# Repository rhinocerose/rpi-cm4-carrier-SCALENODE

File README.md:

# Scalenode platform

Copyright (c) 2020-2021 [Antmicro](https://www.antmicro.com>)

[Home Page](https://opensource.antmicro.com/projects/scalenode)

## Overview

This repository contains the PCB design files for a baseboard supporting Raspberry Pi Compute Module 4.
The baseboard has been optimized for 19-inch rack mount installations for distributed multi-node computing systems.

## Key features

* Supports Raspberry Pi CM4
* Gigabit Ethernet with integrated PoE circuitry
* On-board M.2 (key-M) slot supporting NVMe SSDs 
* Slim PCB outline for 1U chassis
* Expansion connector for peripherals connected over USB
* Expansion connector for HDMI adapters

## Board layout and dimensions

## Design status

The PCB design files were prepared in KiCad.
Prototypes of revision 1.0.0 are now being verified.

## License

[Apache-2.0](LICENSE)

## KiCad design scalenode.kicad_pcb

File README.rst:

==================
Scalenode platform
==================

Copyright (c) 2020-2021 `Antmicro <https://www.antmicro.com>`_

`Home Page <https://opensource.antmicro.com/projects/scalenode>`_

.. figure:: img/scalenode.jpg

Overview
========

This repository contains the PCB design files for a baseboard supporting Raspberry Pi Compute Module 4.
The baseboard has been optimized for 19-inch rack mount installations for distributed multi-node computing systems.

Key features
============

* Supports Raspberry Pi CM4
* Gigabit Ethernet with integrated PoE circuitry
* On-board M.2 (key-M) slot supporting NVMe SSDs 
* Slim PCB outline for 1U chassis
* Expansion connector for peripherals connected over USB
* Expansion connector for HDMI adapters

Board layout and dimensions
===========================

.. image:: img/scalenode-dimensions.png
   :align: center

Design status
=============

The PCB design files were prepared in KiCad.
Prototypes of revision 1.0.0 are now being verified.

License
=======

`Apache-2.0 <LICENSE>`_

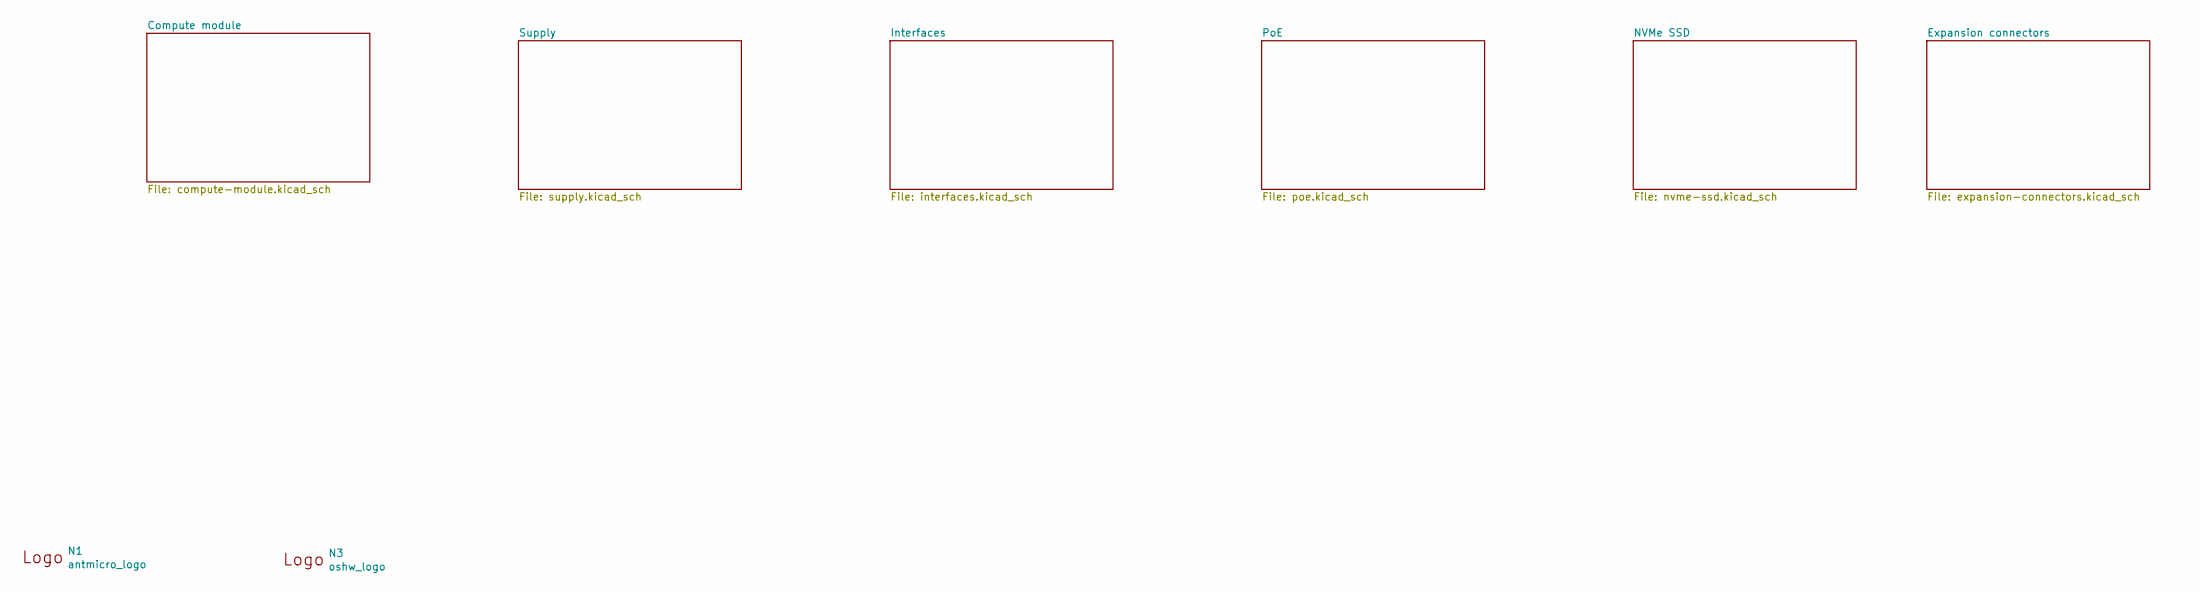
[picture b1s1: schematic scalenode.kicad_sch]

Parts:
N1: antmicro_logo; antmicro-logo_scaled_15mm
N3: oshw_logo; oshw-logo

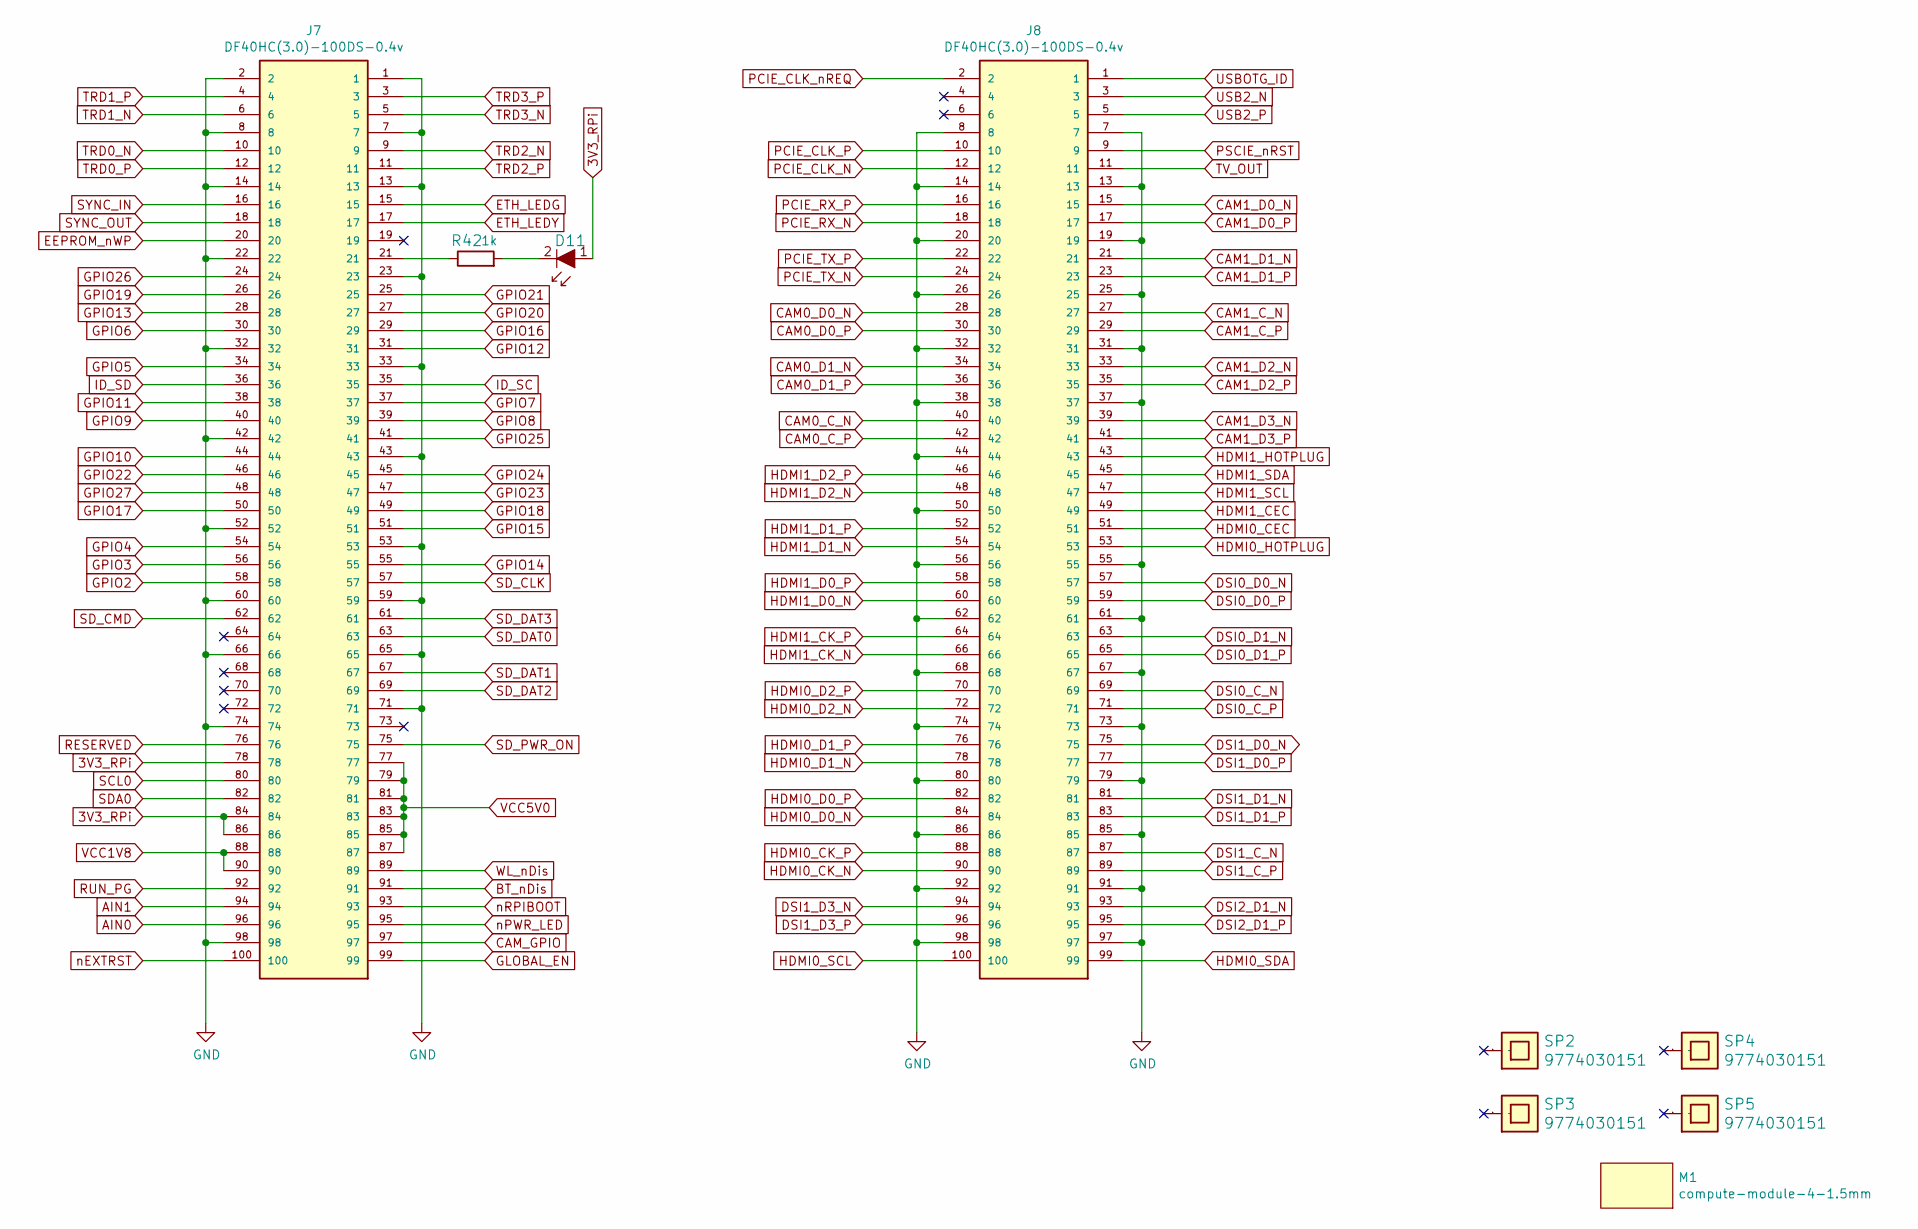
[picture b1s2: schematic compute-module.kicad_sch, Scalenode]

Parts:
D11: KP-1608CGCK; LED_0603; MPN KP-1608CGCK
J7, J8: DF40HC(3.0)-100DS-0.4v; DF40HC-3.0-100DS-0.4v
M1: compute-module-4-1.5mm
R42: R_1k_0603; 0603-res; MPN CR0603-JW-102ELF
SP2, SP3, SP4, SP5: 9774030151; MPN 9774030151

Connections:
AIN0: J7.96
AIN1: J7.94
BT_nDis: J7.91
CAM0_C_N: J8.40
CAM0_C_P: J8.42
CAM0_D0_N: J8.28
CAM0_D0_P: J8.30
CAM0_D1_N: J8.34
CAM0_D1_P: J8.36
CAM1_C_N: J8.27
CAM1_C_P: J8.29
CAM1_D0_N: J8.15
CAM1_D0_P: J8.17
CAM1_D1_N: J8.21
CAM1_D1_P: J8.23
CAM1_D2_N: J8.33
CAM1_D2_P: J8.35
CAM1_D3_N: J8.39
CAM1_D3_P: J8.41
CAM_GPIO: J7.97
DSI0_C_N: J8.69
DSI0_C_P: J8.71
DSI0_D0_N: J8.57
DSI0_D0_P: J8.59
DSI0_D1_N: J8.63
DSI0_D1_P: J8.65
DSI1_C_N: J8.87
DSI1_C_P: J8.89
DSI1_D0_N: J8.75
DSI1_D0_P: J8.77
DSI1_D1_N: J8.81
DSI1_D1_P: J8.83
DSI1_D3_N: J8.94
DSI1_D3_P: J8.96
DSI2_D1_N: J8.93
DSI2_D1_P: J8.95
EEPROM_nWP: J7.20
ETH_LEDG: J7.15; also elsewhere on the board
ETH_LEDY: J7.17; also elsewhere on the board
GLOBAL_EN: J7.99
GND: J7.1, J7.2, J7.7, J7.8, J7.13, J7.14, J7.22, J7.23, J7.32, J7.33, J7.42, J7.43, J7.52, J7.53, J7.59, J7.60, J7.65, J7.66, J7.71, J7.74, J7.98, J8.7, J8.8, J8.13, J8.14, J8.19, J8.20, J8.25, J8.26, J8.31, J8.32, J8.37, J8.38, J8.44, J8.50, J8.55, J8.56, J8.61, J8.62, J8.67, J8.68, J8.73, J8.74, J8.79, J8.80, J8.85, J8.86, J8.91, J8.92, J8.97, J8.98; also elsewhere on the board
GPIO2: J7.58
GPIO3: J7.56; also elsewhere on the board
GPIO4: J7.54
GPIO5: J7.34
GPIO6: J7.30
GPIO7: J7.37
GPIO8: J7.39
GPIO9: J7.40
GPIO10: J7.44
GPIO11: J7.38
GPIO12: J7.31
GPIO13: J7.28
GPIO14: J7.55
GPIO15: J7.51
GPIO16: J7.29
GPIO17: J7.50
GPIO18: J7.49
GPIO19: J7.26
GPIO20: J7.27
GPIO21: J7.25
GPIO22: J7.46
GPIO23: J7.47
GPIO24: J7.45
GPIO25: J7.41
GPIO26: J7.24
GPIO27: J7.48
HDMI0_CEC: J8.51
HDMI0_CK_N: J8.90
HDMI0_CK_P: J8.88
HDMI0_D0_N: J8.84
HDMI0_D0_P: J8.82
HDMI0_D1_N: J8.78
HDMI0_D1_P: J8.76
HDMI0_D2_N: J8.72
HDMI0_D2_P: J8.70
HDMI0_HOTPLUG: J8.53
HDMI0_SCL: J8.100
HDMI0_SDA: J8.99
HDMI1_CEC: J8.49
HDMI1_CK_N: J8.66
HDMI1_CK_P: J8.64
HDMI1_D0_N: J8.60
HDMI1_D0_P: J8.58
HDMI1_D1_N: J8.54
HDMI1_D1_P: J8.52
HDMI1_D2_N: J8.48
HDMI1_D2_P: J8.46
HDMI1_HOTPLUG: J8.43
HDMI1_SCL: J8.47
HDMI1_SDA: J8.45
ID_SC: J7.35
ID_SD: J7.36
unnamed: D11.2, R42.2
unnamed: J7.21, R42.1
PCIE_CLK_N: J8.12; also elsewhere on the board
PCIE_CLK_P: J8.10; also elsewhere on the board
PCIE_CLK_nREQ: J8.2; also elsewhere on the board
PCIE_RX_N: J8.18; also elsewhere on the board
PCIE_RX_P: J8.16; also elsewhere on the board
PCIE_TX_N: J8.24; also elsewhere on the board
PCIE_TX_P: J8.22; also elsewhere on the board
PSCIE_nRST: J8.9; also elsewhere on the board
RESERVED: J7.76
RUN_PG: J7.92
SCL0: J7.80
SDA0: J7.82
SD_CLK: J7.57; also elsewhere on the board
SD_CMD: J7.62; also elsewhere on the board
SD_DAT0: J7.63; also elsewhere on the board
SD_DAT1: J7.67; also elsewhere on the board
SD_DAT2: J7.69; also elsewhere on the board
SD_DAT3: J7.61; also elsewhere on the board
SD_PWR_ON: J7.75
SYNC_IN: J7.16
SYNC_OUT: J7.18
TRD0_N: J7.10; also elsewhere on the board
TRD0_P: J7.12; also elsewhere on the board
TRD1_N: J7.6; also elsewhere on the board
TRD1_P: J7.4; also elsewhere on the board
TRD2_N: J7.9; also elsewhere on the board
TRD2_P: J7.11; also elsewhere on the board
TRD3_N: J7.5; also elsewhere on the board
TRD3_P: J7.3; also elsewhere on the board
TV_OUT: J8.11
USB2_N: J8.3; also elsewhere on the board
USB2_P: J8.5; also elsewhere on the board
USBOTG_ID: J8.1; also elsewhere on the board
VCC1V8: J7.88, J7.90
VCC5V0: J7.77, J7.79, J7.81, J7.83, J7.85, J7.87; also elsewhere on the board
WL_nDis: J7.89
nEXTRST: J7.100
nPWR_LED: J7.95
nRPIBOOT: J7.93

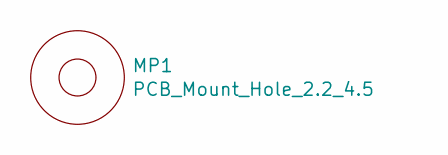
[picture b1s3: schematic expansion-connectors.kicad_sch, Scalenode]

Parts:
MP1: PCB_Mount_Hole_2.2_4.5; mounting-hole-2.2mm

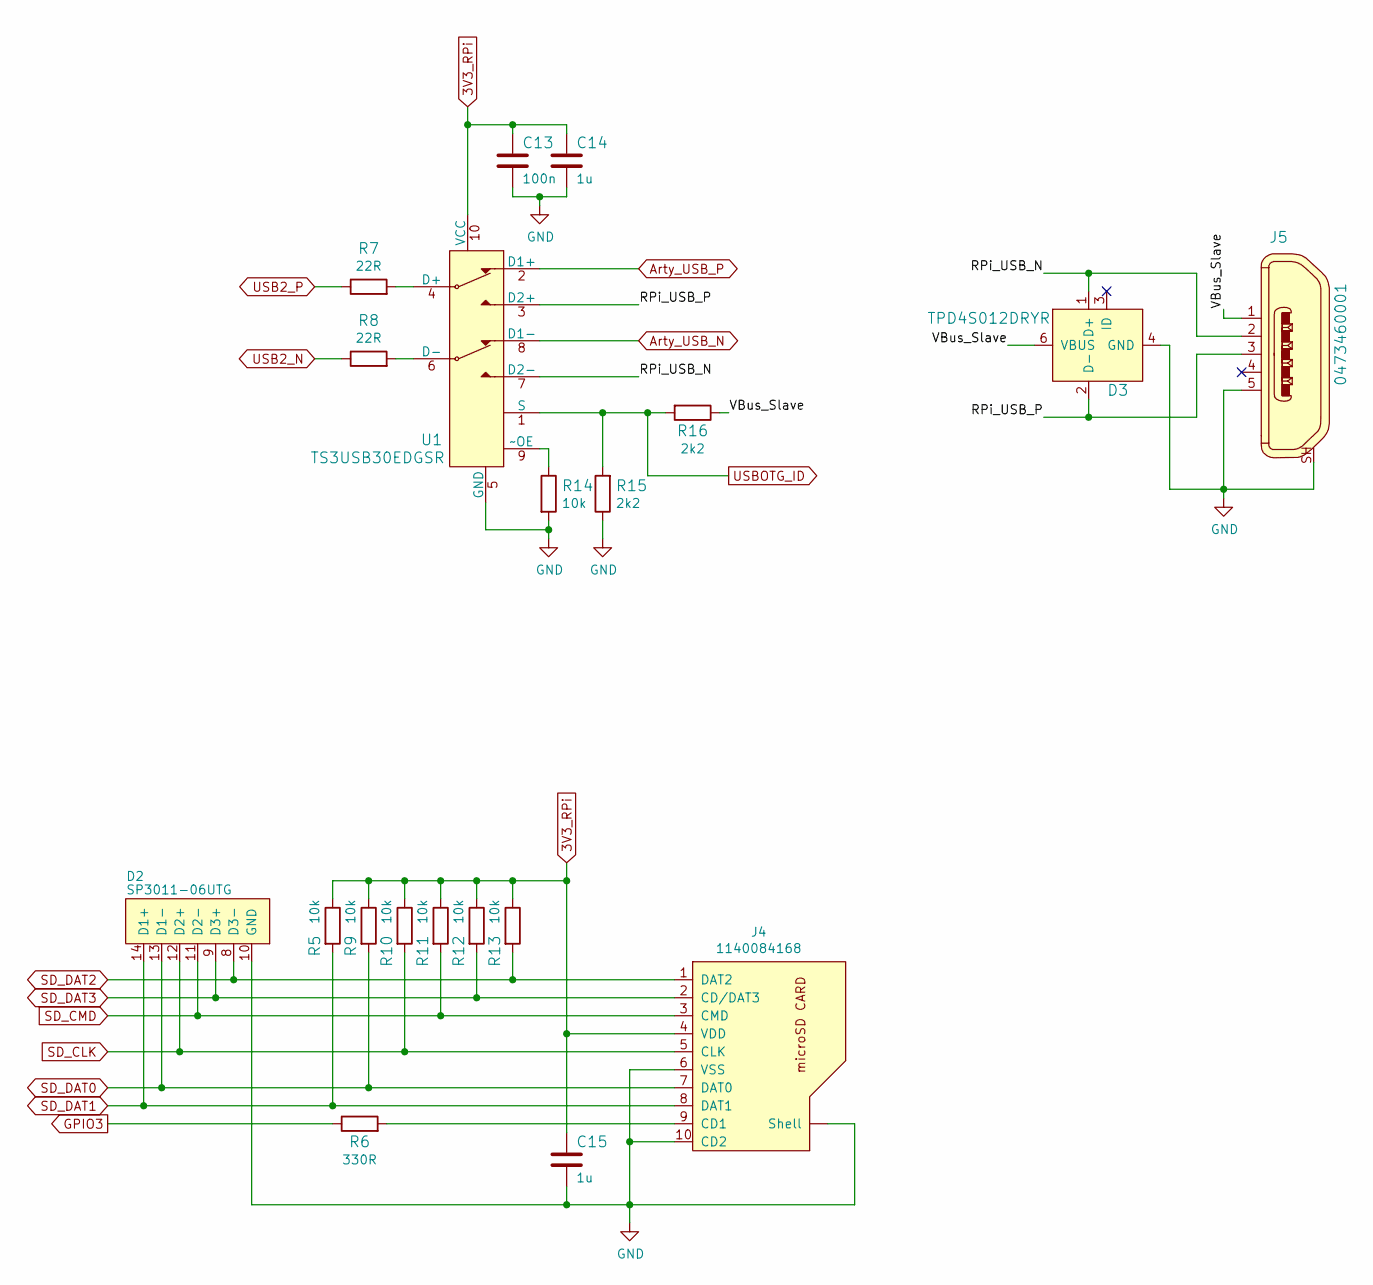
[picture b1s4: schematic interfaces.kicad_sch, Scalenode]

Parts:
C13: C_100n_0402; 0402-cap; MPN 0402X104K6R3CT
C14, C15: C_1u_0402; 0402-cap; MPN C1005X6S1A105K050BC
D2: SP3011-06UTG; SON50P350X135X55-14N; MPN SP3011-06UTG
D3: TPD4S012DRYR; UFDFN-6_1.45x1mm; MPN TPD4S012DRYR
J4: 1140084168; MicroSD_1140084168; MPN 1140084168
J5: 0473460001; USB_Micro_B_Female_0473460001; MPN 0473460001
R5, R9, R10, R11, R12, R13, R14: R_10k_0402; 0402-res; MPN CRCW040210K0FKEDHP
R6: R_330R_0402; 0402-res; MPN MCMR04X3300FTL
R7, R8: R_22R_0402; 0402-res; MPN CRCW040222R0FKED
R15, R16: R_2k2_0402; 0402-res; MPN RC0402FR-072K2L
U1: TS3USB30EDGSR; MSOP-10_W3mm; MPN TS3USB30EDGSR

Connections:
/Interfaces/RPi_USB_N: D3.1 (D+), J5.2, U1.7 (D2-)
/Interfaces/RPi_USB_P: D3.2 (D-), J5.3, U1.3 (D2+)
Arty_USB_N: U1.8 (D1-)
Arty_USB_P: U1.2 (D1+)
GND: C13.2, C14.2, C15.2, D2.10 (GND), D3.4 (GND), J4.6 (VSS), J4.10 (CD2), J4.~ (Shell), J5.5, J5.SH, R14.2, R15.1, U1.5 (GND); also elsewhere on the board
GPIO3: R6.1; also elsewhere on the board
unnamed: J4.9 (CD1), R6.2
unnamed: R7.2, U1.4 (D+)
unnamed: R8.2, U1.6 (D-)
unnamed: R14.1, U1.9 (~OE)
SD_CLK: D2.12 (D2+), J4.5 (CLK), R10.2; also elsewhere on the board
SD_CMD: D2.11 (D2-), J4.3 (CMD), R11.2; also elsewhere on the board
SD_DAT0: D2.13 (D1-), J4.7 (DAT0), R9.2; also elsewhere on the board
SD_DAT1: D2.14 (D1+), J4.8 (DAT1), R5.2; also elsewhere on the board
SD_DAT2: D2.8 (D3-), J4.1 (DAT2), R13.2; also elsewhere on the board
SD_DAT3: D2.9 (D3+), J4.2 (CD/DAT3), R12.2; also elsewhere on the board
USB2_N: R8.1; also elsewhere on the board
USB2_P: R7.1; also elsewhere on the board
USBOTG_ID: R15.2, R16.2, U1.1 (S); also elsewhere on the board

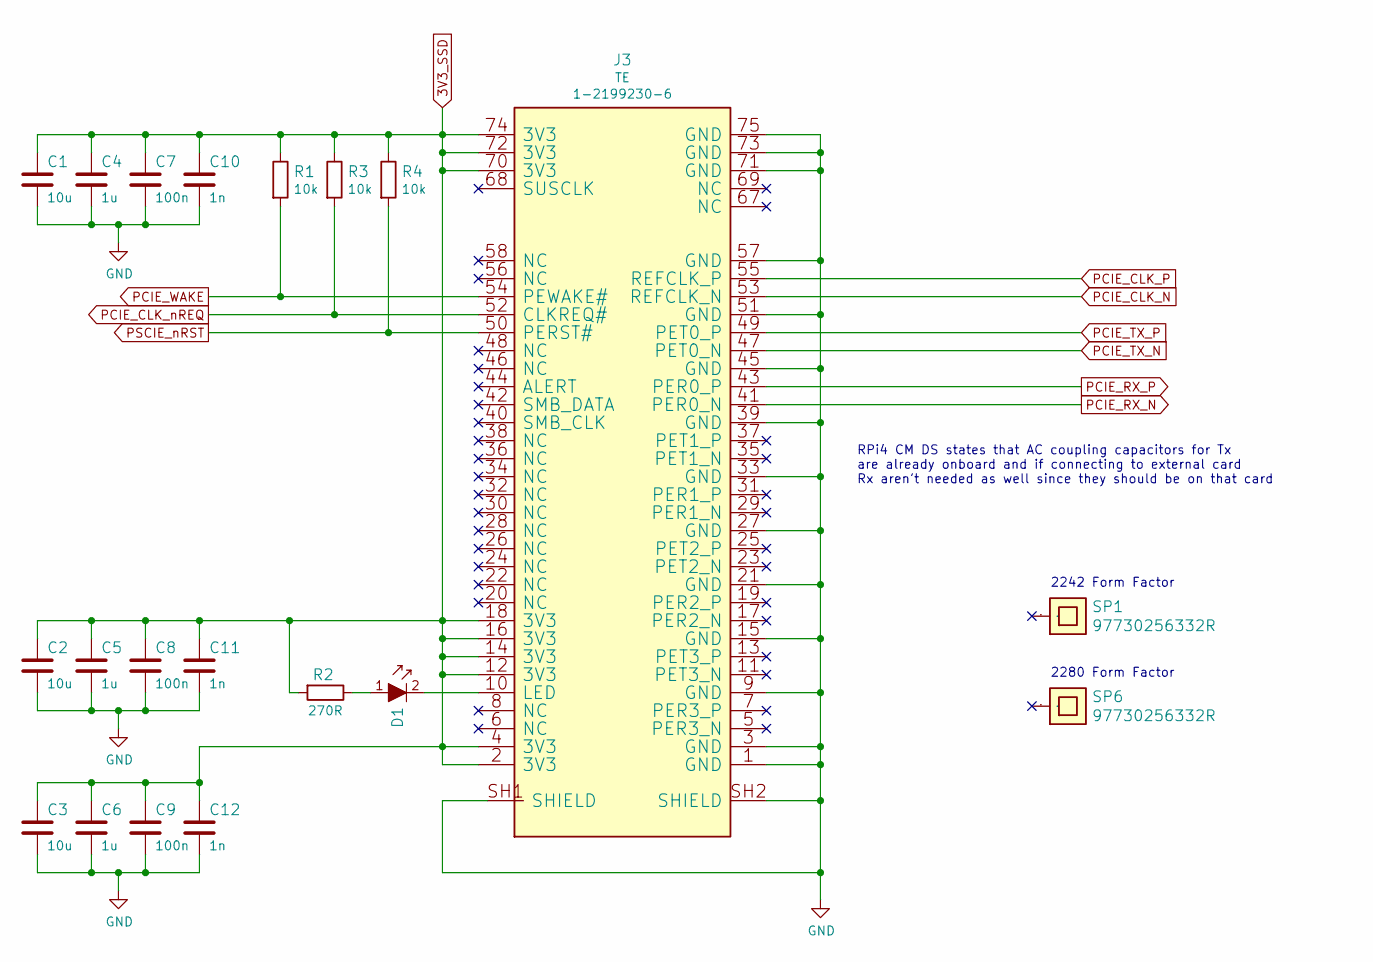
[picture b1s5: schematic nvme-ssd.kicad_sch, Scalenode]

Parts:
C1, C2, C3: C_10u_0603; 0603-cap; MPN GRM188R61A106KE69D
C4, C5, C6: C_1u_0603; 0603-cap; MPN 0603YD105KAT2A
C7, C8, C9: C_100n_0603; 0603-cap; MPN 0603YC104KAZ2A
C10, C11, C12: C_1n_0603; 0603-cap; MPN 06031C102JAT2A
D1: KP-1608CGCK; LED_0603; MPN KP-1608CGCK
J3: 1-2199230-6; MPN 1-2199230-6
R1, R3, R4: R_10k_0603; 0603-res; MPN CR0603-JW-103ELF
R2: R_270R_0603; 0603-res; MPN CRGH0603F270R
SP1, SP6: 97730256332R; MPN 97730256332R

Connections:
3V3_SSD: C1.1, C2.1, C3.1, C4.1, C5.1, C6.1, C7.1, C8.1, C9.1, C10.1, C11.1, C12.1, J3.2 (3V3), J3.4 (3V3), J3.12 (3V3), J3.14 (3V3), J3.16 (3V3), J3.18 (3V3), J3.70 (3V3), J3.72 (3V3), J3.74 (3V3), R1.1, R2.2, R3.1, R4.1; also elsewhere on the board
GND: C1.2, C2.2, C3.2, C4.2, C5.2, C6.2, C7.2, C8.2, C9.2, C10.2, C11.2, C12.2, J3.1 (GND), J3.3 (GND), J3.9 (GND), J3.15 (GND), J3.21 (GND), J3.27 (GND), J3.33 (GND), J3.39 (GND), J3.45 (GND), J3.51 (GND), J3.57 (GND), J3.71 (GND), J3.73 (GND), J3.75 (GND), J3.SH1 (SHIELD), J3.SH2 (SHIELD); also elsewhere on the board
unnamed: D1.1, R2.1
unnamed: D1.2, J3.10 (LED)
PCIE_CLK_N: J3.53 (REFCLK_N); also elsewhere on the board
PCIE_CLK_P: J3.55 (REFCLK_P); also elsewhere on the board
PCIE_CLK_nREQ: J3.52 (CLKREQ#), R3.2; also elsewhere on the board
PCIE_RX_N: J3.41 (PER0_N); also elsewhere on the board
PCIE_RX_P: J3.43 (PER0_P); also elsewhere on the board
PCIE_TX_N: J3.47 (PET0_N); also elsewhere on the board
PCIE_TX_P: J3.49 (PET0_P); also elsewhere on the board
PCIE_WAKE: J3.54 (PEWAKE#), R1.2
PSCIE_nRST: J3.50 (PERST#), R4.2; also elsewhere on the board

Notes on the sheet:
RPi4 CM DS states that AC coupling capacitors for Tx are already onboard and if connecting to external card Rx aren't needed as well since they should be on that card
2242 Form Factor
2280 Form Factor

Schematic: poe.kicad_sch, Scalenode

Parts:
C20, C21, C23, C24: C_10n_0402; 0402-cap; MPN 04025G103ZAT2A
C22, C25, C50: C_1n_1210_2kV; 1210-cap; MPN C1210C102KGRACTU
C26: C_10n_0603; 0603-cap; MPN 06031C103JAT2A
C27: C_270p_0603; 0603-cap; MPN MC0603B271K500CT
C28: C_100n_0805_100V; 0805-cap; MPN CL21B104KCFNNNE
C29: C_47u_ELEC_100V; CP_Elec_10x10.5; MPN EEEHA2A470UP
C30: C_100n_0603; 0603-cap; MPN 0603YC104KAZ2A
C31: C_220n_0603_25V; 0603-cap; MPN C1608X5R1H474K080AB
C32, C34, C36: C_1u_1210_100V; 1210-cap; MPN 12101C105K4Z2A
C33: C_22u_ELEC_25V; CP_Elec_5x5.8; MPN EEEFK1E220R
C35, C43, C47: C_1u_0603; 0603-cap; MPN 0603YD105KAT2A
C37, C40: C_470n_0603; 0603-cap; MPN C1608X5R1H474K080AB
C38: C_100p_0402; 0402-cap; MPN 0402N101J500CT
C39: C_82n_0603; 0603-cap; MPN MC0603B823K500CT
C41, C42, C44: C_47u_0603; 0603-cap; MPN GRM188R60J476ME15D
C45, C46: C_220u_KEMET_B; KEMET_B; MPN TMCMB0J227MTRF
C48: C_1n_0603; 0603-cap; MPN 06031C102JAT2A
C49: C_1n2_0603; 0603-res; MPN C0603C122K5RACTU
D4, D5: MB10S; MPN MB10S
D6: SMAJ58A-13-F; DO-214AC; MPN SMAJ58A-13-F
D7, D9: BAS16E6327HTSA1; SOT-23-3; MPN BAS16E6327HTSA1
D8: KP-1608CGCK; LED_0603; MPN KP-1608CGCK
D10: MURA120T3G; DO-214AC; MPN MURA120T3G
D12: TLV431ACDBVR; SOT-23-5; MPN TLV431ACDBVR
D13, D14: BAV99W,115; SOT-323; MPN BAV99W,115
FB1, FB2: BLM21PG221SN1D; 0805-res; MPN BLM21PG221SN1D
IC2: TPS2378DDA; SOIC127P600X170-9N; MPN TPS2378DDA; Mouser Part Number 595-TPS2378DDA
J6: SS-74800-144; MPN SS-74800-144
L3: H6096NL; SOIC127P1594X685-24N; MPN H6096NL
L4: DO1608C-332MLB; L_6.3x4.5; MPN DO1608C-332MLB
L5: DR74-R33-R; L_DR74; MPN DR74-R33-R
Q1, Q2, Q5: MMBT3906,215; SOT-23-3; MPN MMBT3906,215
Q3: SI7848BDP-T1-E3; PowerPAK_SO-8_Single; MPN SI7848BDP-T1-E3
Q4: SI7450DP-T1-GE3; PowerPAK_SO-8_Single; MPN SI7450DP-T1-GE3
R17: R_0R_1206; 1206-res; MPN MCMR12X000_PTL
R21, R22: R_220R_0402; 0402-res; MPN ERJ2GEJ221X
R23, R24, R25, R26, R27, R28, R29, R30: R_75R_0402; 0402-res; MPN RC0402FR-0775RL
R31: R_10k7_0603; 0603-res; MPN CRCW060310K7FKEA
R32, R35, R47, R49: R_10k_0603; 0603-res; MPN CR0603-JW-103ELF
R33: R_4k64_0603; 0603-res; MPN CRCW06034K64FKEA
R34: R_63R4_0402; 0402-res; MPN CRCW040263R4FKED
R36: R_24k9_0402; 0402-res; MPN WR04X2492FTL
R37: R_30k1_0603; 0603-res; MPN CRCW060330K1FKEA
R38: R_4k99_0402; 0402-res; MPN MCMR04X4991FTL
R39: R_24R9_0603; 0603-res; MPN CRCW060324R9FKEA
R40: R_15k_0603; 0603-res; MPN CR0603-FX-1502ELF
R41: R_20R_0603; 0603-res; MPN CRCW060320R0FKEA
R43: R_R33_2512; 2512; MPN RLP73K3AR33JTE
R44: R_1k_0402; 0402-res; MPN CR0402-FX-1001GLF
R45, R46: R_1k_0603; 0603-res; MPN CR0603-JW-102ELF
R48, R53: R_49R9_0603; 0603-res; MPN CRCW060349R9FKEA
R50: R_10R_2010; 2010-res; MPN WF20P10R0FTL
R51, R54: R_41k2_0603; 0603-res; MPN CRCW060341K2FKEA
R52: R_13k3_0603; 0603-res; MPN CRCW060313K3FKEA
T1: P0926NL; Pulse_P0926NL; MPN P0926
T2: POE300F-50L; POE300F-24LD; MPN POE300F-50L
TP3, TP4, TP5, TP6: TP_SMD1MM; Testpoint_smd_1mm
U3: UCC3809D2; SOIC-8_W3.9mm; MPN UCC3809D2
U4: TCMT1107; MPN TCMT1107

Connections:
/PoE/CDB: C26.1, IC2.6 (CDB), U3.2 (SS)
/PoE/CTRL_FB: C38.1, R35.1, R44.2, R45.1, U3.1 (FB)
/PoE/CTRL_OUT: C37.2, R39.1, U3.6 (OUT)
/PoE/CTRL_REF: C35.1, R38.1, U3.8 (REF), U4.4
/PoE/CTRL_VDD: C31.1, C33.1, D7.3, D8.1, R37.2, TP3.1, U3.7 (VDD)
/PoE/PAIR12: C20.1, D4.3, L3.24 (MCT1)
/PoE/PAIR36: C21.1, D4.4, L3.21 (MCT2)
/PoE/PAIR45: C23.1, D5.3, L3.18 (MCT3)
/PoE/PAIR78: C24.1, D5.4, L3.15 (MCT4)
/PoE/T_ETH_D0_N: J6.2, L3.22 (MX1-)
/PoE/T_ETH_D0_P: J6.1, L3.23 (MX1+)
/PoE/T_ETH_D1_N: J6.6, L3.19 (MX2-)
/PoE/T_ETH_D1_P: J6.3, L3.20 (MX2+)
/PoE/T_ETH_D2_N: J6.5, L3.16 (MX3-)
/PoE/T_ETH_D2_P: J6.4, L3.17 (MX3+)
/PoE/T_ETH_D3_N: J6.8, L3.13 (MX4-)
/PoE/T_ETH_D3_P: J6.7, L3.14 (MX4+)
ETH_LEDG: J6.11; also elsewhere on the board
ETH_LEDY: J6.9; also elsewhere on the board
GND: C25.1, C41.2, C42.2, C43.2, C44.2, C45.2, C46.2, C47.2, C48.1, C50.1, D12.5 (A), D14.1, Q3.1 (S), Q3.2 (S), Q3.3 (S), Q5.3, R17.2, R47.2, R52.2, T1.2, T1.3, TP5.1; also elsewhere on the board
GNDD: C26.2, C27.2, C29.2, C31.2, C32.2, C33.2, C34.2, C35.2, C38.2, C39.2, IC2.5 (RTN), IC2.8 (APD), Q1.3, Q2.3, R43.2, T1.6, T2.5, U3.5 (GND)
unnamed: C20.2, R23.1
unnamed: C21.2, R24.1
unnamed: C22.1, R23.2, R24.2, R25.2, R26.2
unnamed: C23.2, R25.1
unnamed: C24.2, R26.1
unnamed: C25.2, R27.1, R28.1, R29.1, R30.1
unnamed: C27.1, Q1.1, R31.2, R33.2
unnamed: C30.1, Q1.2, R38.2
unnamed: C30.2, R35.2
unnamed: C32.1, C34.1, C36.1, L4.2, R37.1, R40.1, T2.1, T2.2
unnamed: C36.2, D10.K, R40.2
unnamed: C37.1, T1.1
unnamed: C39.1, R45.2, U4.3
unnamed: C40.1, R47.1, R48.2
unnamed: C40.2, T1.4, T1.5
unnamed: C41.1, C42.1, C44.1, C45.1, L5.1, T2.7, T2.8, T2.9
unnamed: C43.1, D13.3, R49.2
unnamed: C48.2, R50.2
unnamed: C49.1, D12.4 (REF), R52.1, R54.2
unnamed: C49.2, R51.2
unnamed: D4.1, D5.1, FB2.1
unnamed: D4.2, D5.2, FB1.1
unnamed: D7.1, R41.1
unnamed: D8.2, R32.1
unnamed: D9.1, Q2.1, R39.2
unnamed: D9.3, Q2.2, Q4.4 (G)
unnamed: D10.A, Q4.5 (D), T2.3, T2.4
unnamed: D12.3 (K), D13.1, R51.1, U4.2
unnamed: D14.2, Q3.4 (G), Q5.2
unnamed: D14.3, Q5.1, R48.1
unnamed: IC2.2 (DEN), R36.2
unnamed: IC2.3 (CLS), R34.1
unnamed: IC2.7 (T2P), R32.2
unnamed: J6.10, R21.1
unnamed: J6.12, R22.1
unnamed: L3.1 (TCT1), R27.2
unnamed: L3.4 (TCT2), R28.2
unnamed: L3.7 (TCT3), R29.2
unnamed: L3.10 (TCT4), R30.2
unnamed: Q3.5 (D), R50.1, T2.10, T2.11, T2.12
unnamed: Q4.1 (S), Q4.2 (S), Q4.3 (S), R43.1, R44.1
unnamed: R31.1, U3.3 (RT1)
unnamed: R33.1, U3.4 (RT2)
unnamed: R41.2, T2.6
unnamed: R46.2, U4.1
unnamed: R53.2, R54.1, TP6.1
TRD0_N: L3.3 (TD1-); also elsewhere on the board
TRD0_P: L3.2 (TD1+); also elsewhere on the board
TRD1_N: L3.6 (TD2-); also elsewhere on the board
TRD1_P: L3.5 (TD2+); also elsewhere on the board
TRD2_N: L3.9 (TD3-); also elsewhere on the board
TRD2_P: L3.8 (TD3+); also elsewhere on the board
TRD3_N: L3.12 (TD4-); also elsewhere on the board
TRD3_P: L3.11 (TD4+); also elsewhere on the board
VCC5V0: C46.1, C47.1, D13.2, L5.2, R46.1, R49.1, R53.1, TP4.1; also elsewhere on the board
VDD: C28.1, C29.1, D6.K, FB2.2, IC2.1 (VDD), L4.1, R36.1
VSS: C28.2, D6.A, FB1.2, IC2.4 (VSS), IC2.9 (EP), R34.2

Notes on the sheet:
DNP

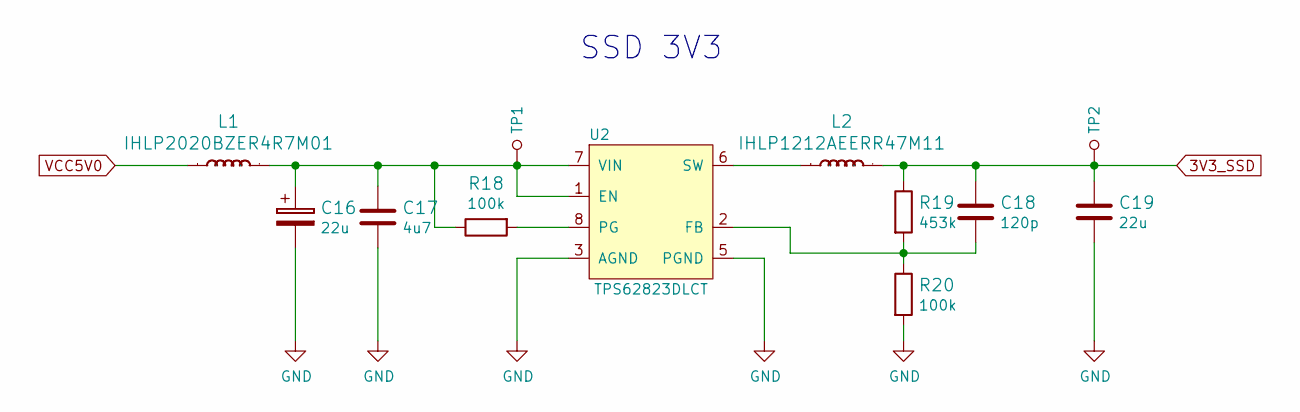
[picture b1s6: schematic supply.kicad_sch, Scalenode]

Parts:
C16: C_22u_KEMET_A; KEMET_A; MPN T491A226K006AT
C17: C_4u7_0603; 0603-cap; MPN C1608X5R1V475M080AC
C18: C_120p_0402; 0402-res; MPN C0402C121J5GACTU
C19: C_22u_1210; 1210-cap; MPN 1210YD226MAT2A
L1: IHLP2020BZER4R7M01; MPN IHLP1212AEERR47M11
L2: IHLP1212AEERR47M11; IHLP-1212AE; MPN IHLP1212AEERR47M11
R18: R_100k_0603; 0603-res; MPN CR0603-FX-1003HLF
R19: R_453k_0402; 0402-res; MPN CRCW0402453KFKED
R20: R_100k_0402; 0402-res; MPN CRCW0402100KFKEDHP
TP1, TP2: TP_SMD1MM; Testpoint_smd_1mm
U2: TPS62823DLCT; QFN-8_2x1mm; MPN TPS62823DLCT

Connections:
3V3_SSD: C18.1, C19.1, L2.2, R19.1, TP2.1; also elsewhere on the board
GND: C16.2, C17.2, C19.2, R20.2, U2.3 (AGND), U2.5 (PGND); also elsewhere on the board
unnamed: C16.1, C17.1, L1.2, R18.1, TP1.1, U2.1 (EN), U2.7 (VIN)
unnamed: C18.2, R19.2, R20.1, U2.2 (FB)
unnamed: L2.1, U2.6 (SW)
unnamed: R18.2, U2.8 (PG)
VCC5V0: L1.1; also elsewhere on the board

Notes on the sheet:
SSD 3V3

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
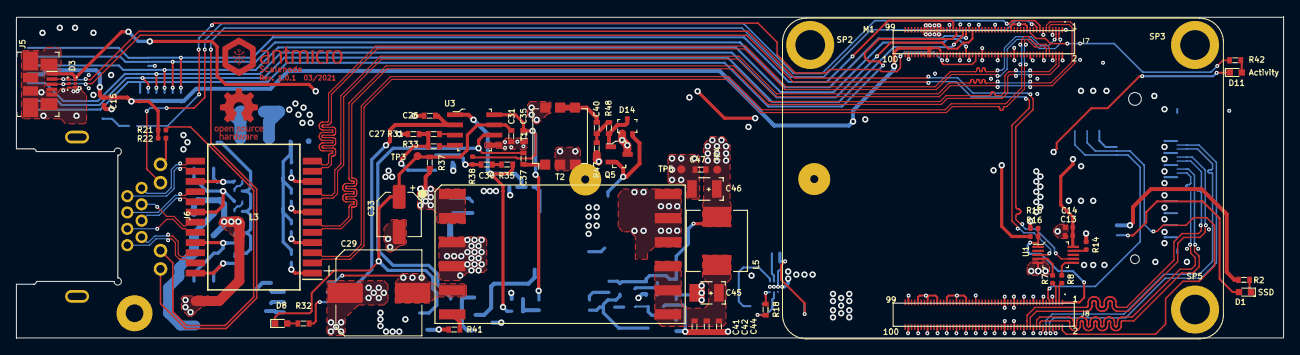
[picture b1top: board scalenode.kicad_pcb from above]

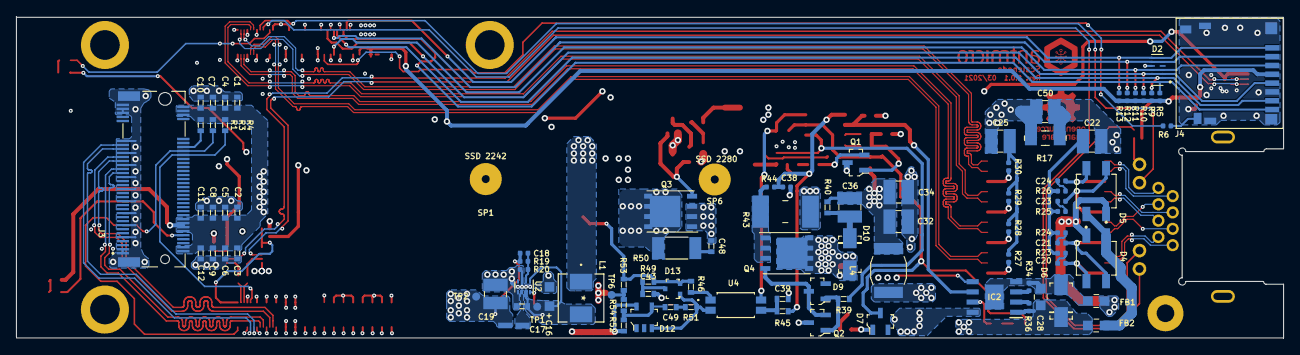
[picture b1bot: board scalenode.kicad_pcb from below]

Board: 4 copper layers, 158.1 x 40.2 mm, 158 parts (95 on the bottom side), 115 nets.

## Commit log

2021-08-16 Removed USB
2021-08-16 Moved CM4 board, rerouted power

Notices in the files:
parts and their libraries:
Copyright 2016 Accelerated Designs. All rights reserved.
